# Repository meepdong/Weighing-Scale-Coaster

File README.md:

# Weighing Scale Coaster
A precision coffee scale built around the HX711 load cell amplifier, optimized for responsiveness and stability. Designed for baristas, tinkerers, and embedded engineers who care about both performance and personality.

## Features
• 	HX711-based load cell interface with high-resolution weight readings

• 	Reference-inspired filtering pipeline adapted from Analog Devices' weigh scale design

• 	OLED display with expressive dome-shaped eyes and smile animation

• 	Timer with short press toggle and long press reset

• 	Flicker-free weight display using hysteresis and trimmed averaging

• 	Designed for both Raspberry Pi Pico W and Seeed Studio XIAO ESP32-C6

## Hardware Overview
### Components
• 	HX711 Load Cell Amplifier

• 	5 kg Load Cell

• 	SSD1306 OLED Display (128×32)

• 	Two momentary push buttons (Tare + Timer) . To be replaced with capacitive touch 

• 	Microcontroller: Raspberry Pi Pico W or Seeed Studio XIAO ESP32-C6

## Wiring Table

| Pin on OLED       | Pin on HX711 | Pin on Pico W | Pin on XIAO ESP32-C6 |
|---------------|--------------|----------------|----------------------|
| VCC           | VCC          | 3.3V           | 3.3V                 |
| GND           | GND          | GND            | GND                  |    
| Data (DT)     | DT           | GPIO 16        | GPIO 10              |
| Clock (SCK)   | SCK          | GPIO 17        | GPIO 11              |
| OLED SDA      | SDA          | GPIO 4         | GPIO 4               |    
| OLED SCL      | SCL          | GPIO 5         | GPIO 5               |
| Tare Button   | -            | GPIO 18        | GPIO 6               |
| Timer Button  | -            | GPIO 19        | GPIO 7               |

## Load Cell Algorithm
This project adapts the signal processing architecture from Analog Devices' weigh scale reference design to the HX711.
Filtering Pipeline

• 	Trimmed Moving Average: Removes min/max outliers from a rolling window to suppress noise while preserving step response.

• 	Step Detection: Detects real weight changes using dual-threshold logic and pre-fills the filter buffer to skip lag.

• 	Display Hysteresis: Prevents flicker by suppressing small changes below a threshold.

### Why It Works
• 	HX711 is a 24-bit sigma-delta ADC with built-in gain and ratiometric measurement.

• 	Filtering compensates for its limited noise-free resolution and slow sample rate.

• 	The result: smooth, stable, and responsive weight readings even with low-cost hardware.

## User Interaction

OLED shows timer and weight. Startup animation includes blinking eyes and a smile. A Hall effect sensor to be integrated for a lid-activated deep sleep and wake mode.

Future Improvements
• 	Calibration helper script for computing 

• 	BLE or Wi-Fi integration for remote brew tracking

• 	Capacitive touch buttons

Credits
Built by Maurice D'Moss, mechanical product design engineer with a passion for coffee and embedded systems.
Filtering architecture inspired by Analog Devices' weigh scale reference design.

## License

This project is licensed under the [Creative Commons Attribution-NonCommercial 4.0 International License](https://creativecommons.org/licenses/by-nc/4.0/).

You are free to use, modify, and share this project for personal and educational purposes.  
Commercial use is not permitted without explicit permission from the author.

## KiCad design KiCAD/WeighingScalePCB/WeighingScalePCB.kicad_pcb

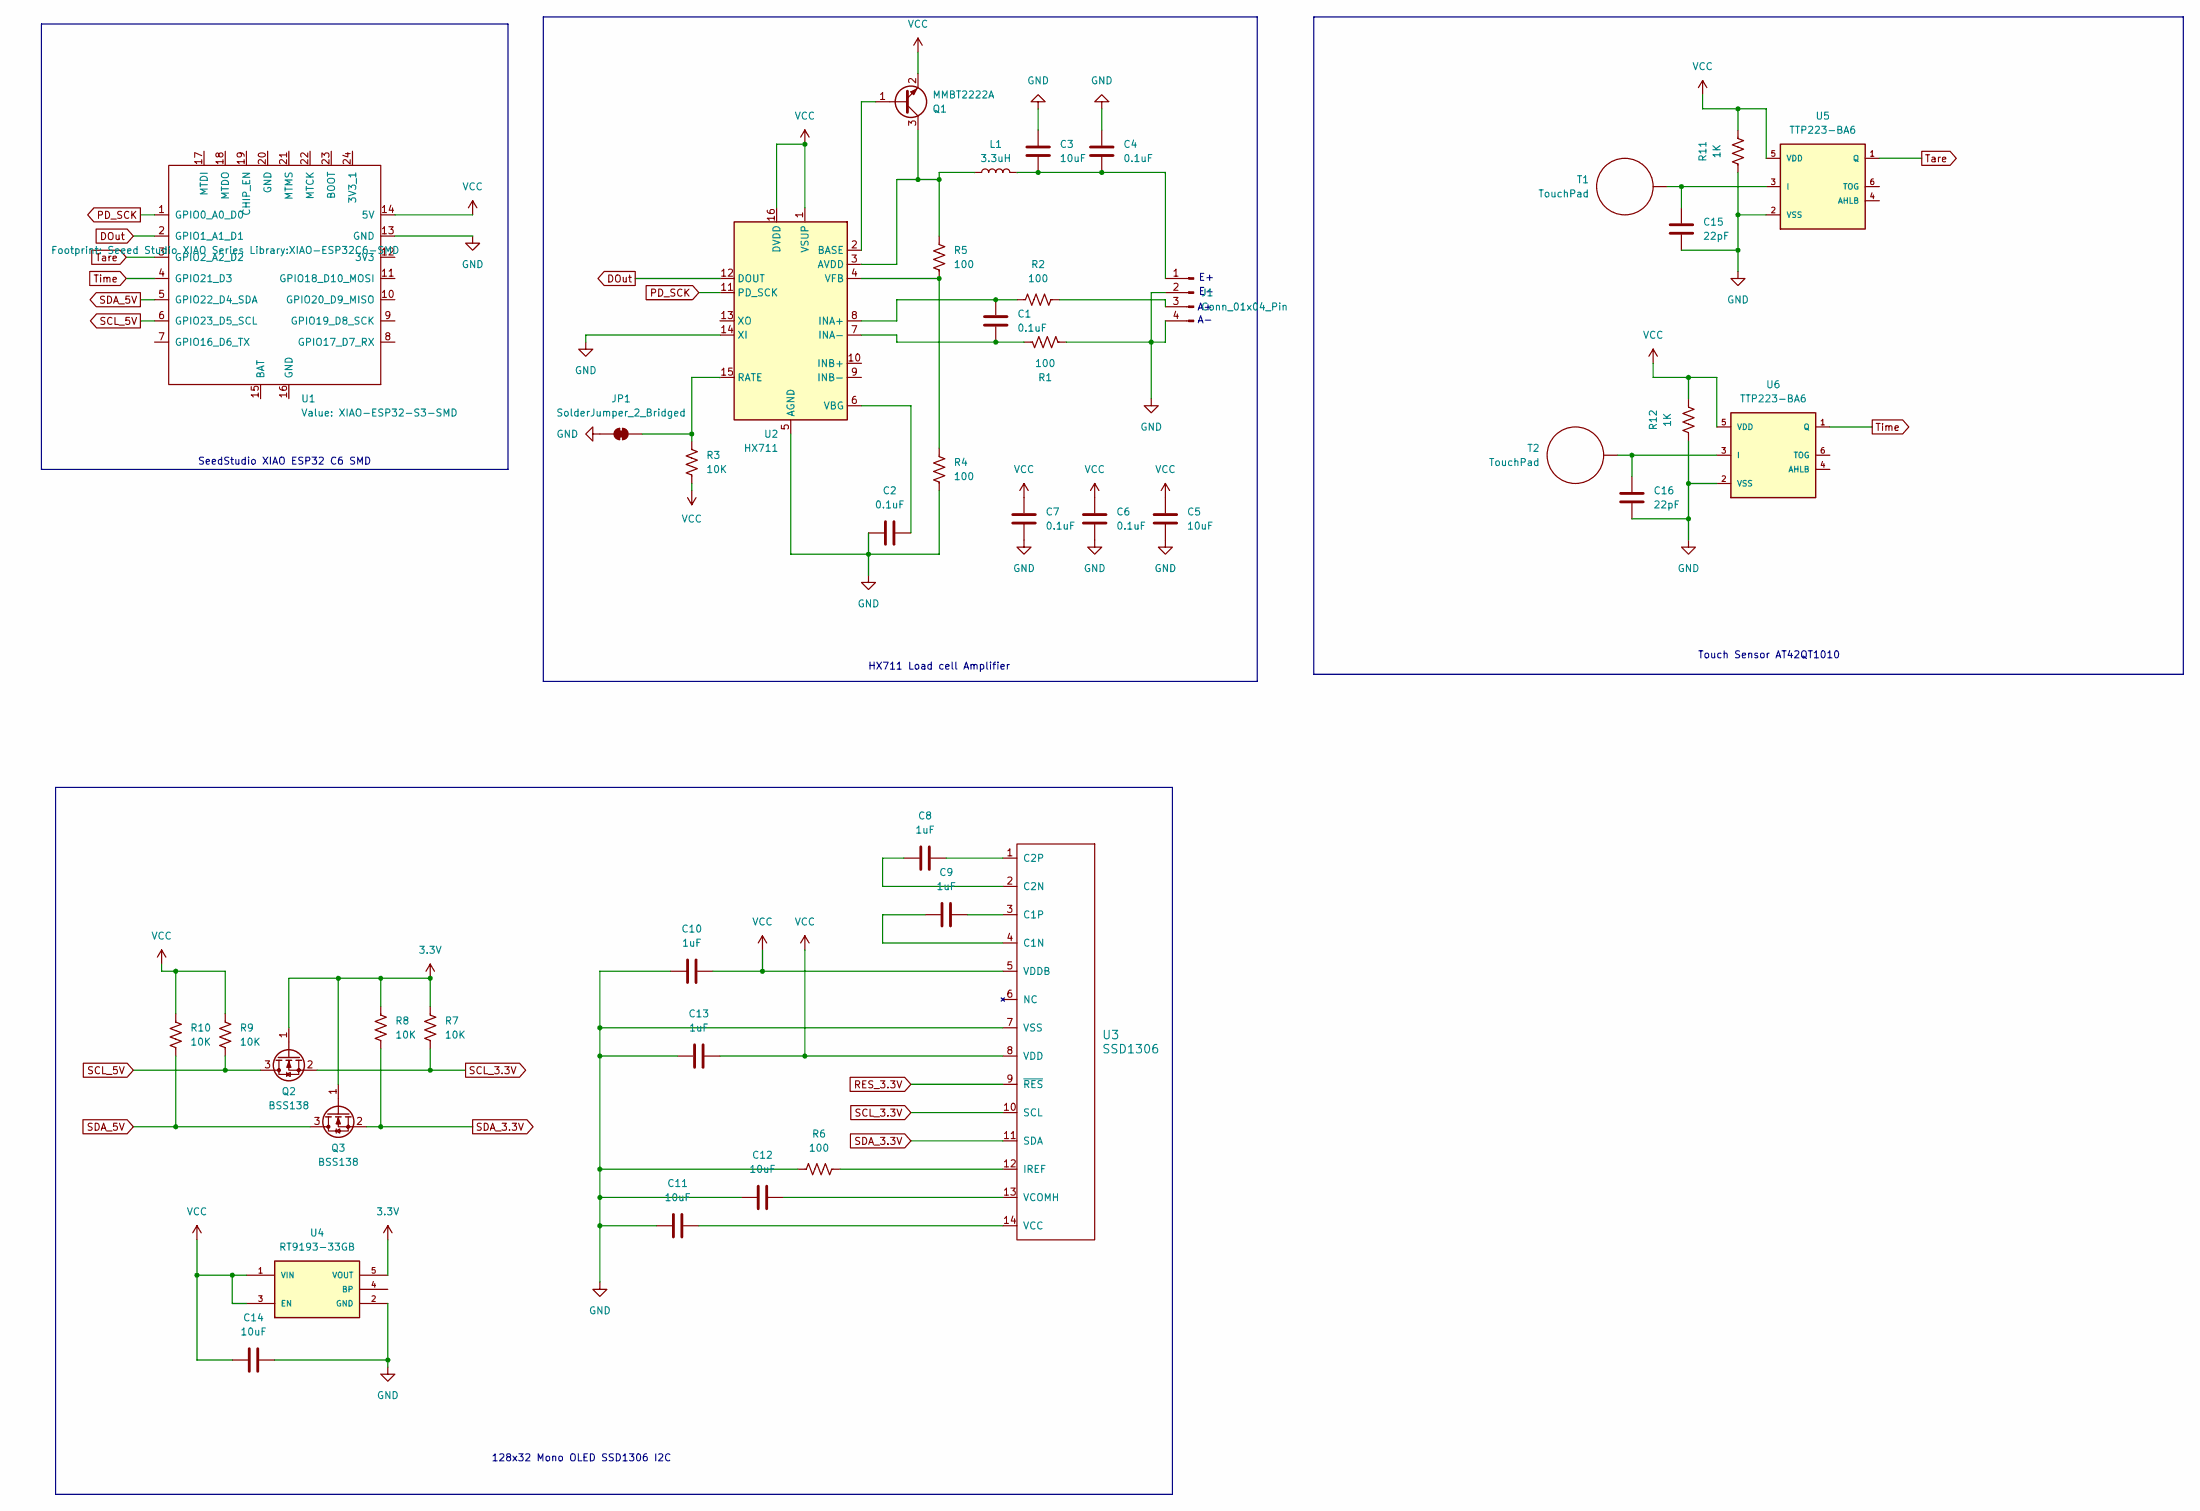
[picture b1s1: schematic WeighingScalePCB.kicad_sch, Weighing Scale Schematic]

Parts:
C1, C2, C4, C6, C7: 0.1uF; C_0402_1005Metric
C3, C5, C11, C12, C14: 10uF; C_0402_1005Metric
C8, C9, C10, C13: 1uF; C_0402_1005Metric
C15, C16: 22pF; C_0402_1005Metric
J1: Conn_01x04_Pin; PinHeader_1x04_P1.00mm_Vertical
JP1: SolderJumper_2_Bridged
L1: 3.3uH; L_Coilcraft_XxL4040
Q1: MMBT2222A; SOT-23
Q2, Q3: BSS138; SOT-23
R1, R2, R4, R5, R6: 100; R_0402_1005Metric
R3, R7, R8, R9, R10: 10K; R_0402_1005Metric
R11, R12: 1K; R_0402_1005Metric
T1, T2: TouchPad; Touch-Pad_10mm
U1: XIAO-ESP32-S3-SMD; XIAO-ESP32C6-SMD
U2: HX711; SOIC-16_3.9x9.9mm_P1.27mm
U3: SSD1306; SSD1306_OLED-0.91-128x32
U4: RT9193-33GB; SOT94P279X129-5N
U5, U6: TTP223-BA6; SOT23-6

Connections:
3.3V: Q2.1 (G), Q3.1 (G), R7.1, R8.1, U4.5 (VOUT)
DOut: U1.2 (GPIO1_A1_D1), U2.12 (DOUT)
GND: C2.1, C3.1, C4.1, C5.2, C6.2, C7.2, C10.1, C11.1, C12.1, C13.1, C14.2, C15.2, C16.2, J1.2, J1.4, JP1.1 (A), R1.1, R4.2, R6.2, R11.2, R12.2, U1.13 (GND), U2.5 (AGND), U2.14 (XI), U3.7 (VSS), U4.2 (GND), U5.2 (VSS), U6.2 (VSS)
unnamed: C3.2, C4.2, J1.1, L1.2
unnamed: J1.3, R2.1
unnamed: JP1.2 (B), R3.1, U2.15 (RATE)
unnamed: Q1.1 (B), U2.2 (BASE)
unnamed: L1.1, Q1.3 (C), R5.1, U2.3 (AVDD)
unnamed: C1.1, R2.2, U2.8 (INA+)
unnamed: C1.2, R1.2, U2.7 (INA-)
unnamed: C2.2, U2.6 (VBG)
unnamed: R4.1, R5.2, U2.4 (VFB)
unnamed: C9.1, U3.4 (C1N)
unnamed: C9.2, U3.3 (C1P)
unnamed: C8.1, U3.2 (C2N)
unnamed: C8.2, U3.1 (C2P)
unnamed: R6.1, U3.12 (IREF)
unnamed: C11.2, U3.14 (VCC)
unnamed: C12.2, U3.13 (VCOMH)
unnamed: C15.1, T1.1 (Pad), U5.3 (I)
unnamed: C16.1, T2.1 (Pad), U6.3 (I)
PD_SCK: U1.1 (GPIO0_A0_D0), U2.11 (PD_SCK)
RES_3.3V: U3.9 (~RES)
SCL_3.3V: Q2.2 (S), R7.2, U3.10 (SCL)
SCL_5V: Q2.3 (D), R9.2, U1.6 (GPIO23_D5_SCL)
SDA_3.3V: Q3.2 (S), R8.2, U3.11 (SDA)
SDA_5V: Q3.3 (D), R10.2, U1.5 (GPIO22_D4_SDA)
Tare: U1.3 (GPIO2_A2_D2), U5.1 (Q)
Time: U1.4 (GPIO21_D3), U6.1 (Q)
VCC: C5.1, C6.1, C7.1, C10.2, C13.2, C14.1, Q1.2 (E), R3.2, R9.1, R10.1, R11.1, R12.1, U1.14 (5V), U2.1 (VSUP), U2.16 (DVDD), U3.5 (VDDB), U3.8 (VDD), U4.1 (VIN), U4.3 (EN), U5.5 (VDD), U6.5 (VDD)

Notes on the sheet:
HX711 Load cell Amplifier
SeedStudio XIAO ESP32 C6 SMD
Touch Sensor AT42QT1010
128x32 Mono OLED SSD1306 I2C

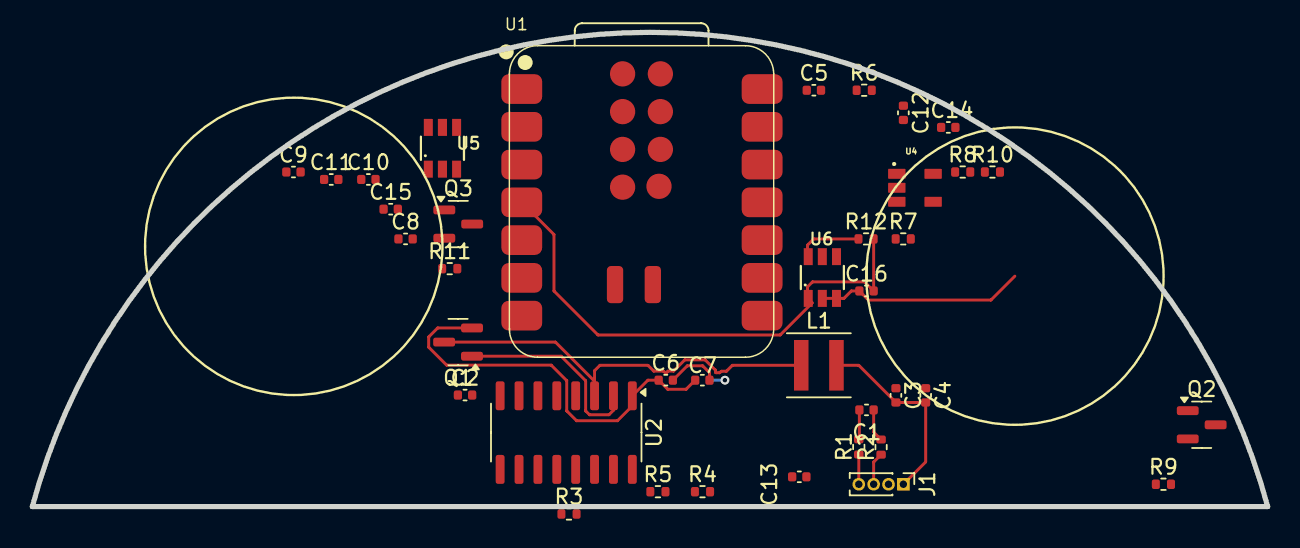
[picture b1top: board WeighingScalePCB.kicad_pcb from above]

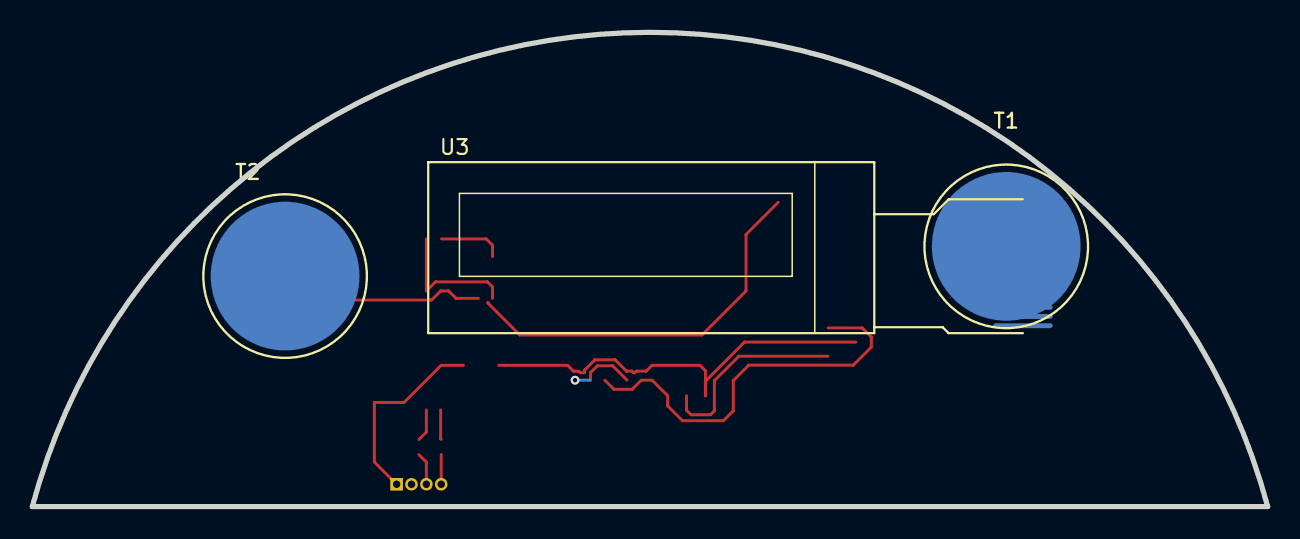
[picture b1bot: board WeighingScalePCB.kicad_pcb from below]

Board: 4 copper layers, 83.1 x 31.9 mm, 41 parts (3 on the bottom side), 29 nets.

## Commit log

2025-09-17 changed Render Image to v1
2025-09-18 Updated main.py in Firmware directory
2025-09-18 Added README
2025-09-18 Updates to README
2025-09-18 Added LICENSE file and license section to README.md
2025-09-18 Changes to README
2025-10-02 prl commit
2025-10-05 updated symbol libraries for connectors
